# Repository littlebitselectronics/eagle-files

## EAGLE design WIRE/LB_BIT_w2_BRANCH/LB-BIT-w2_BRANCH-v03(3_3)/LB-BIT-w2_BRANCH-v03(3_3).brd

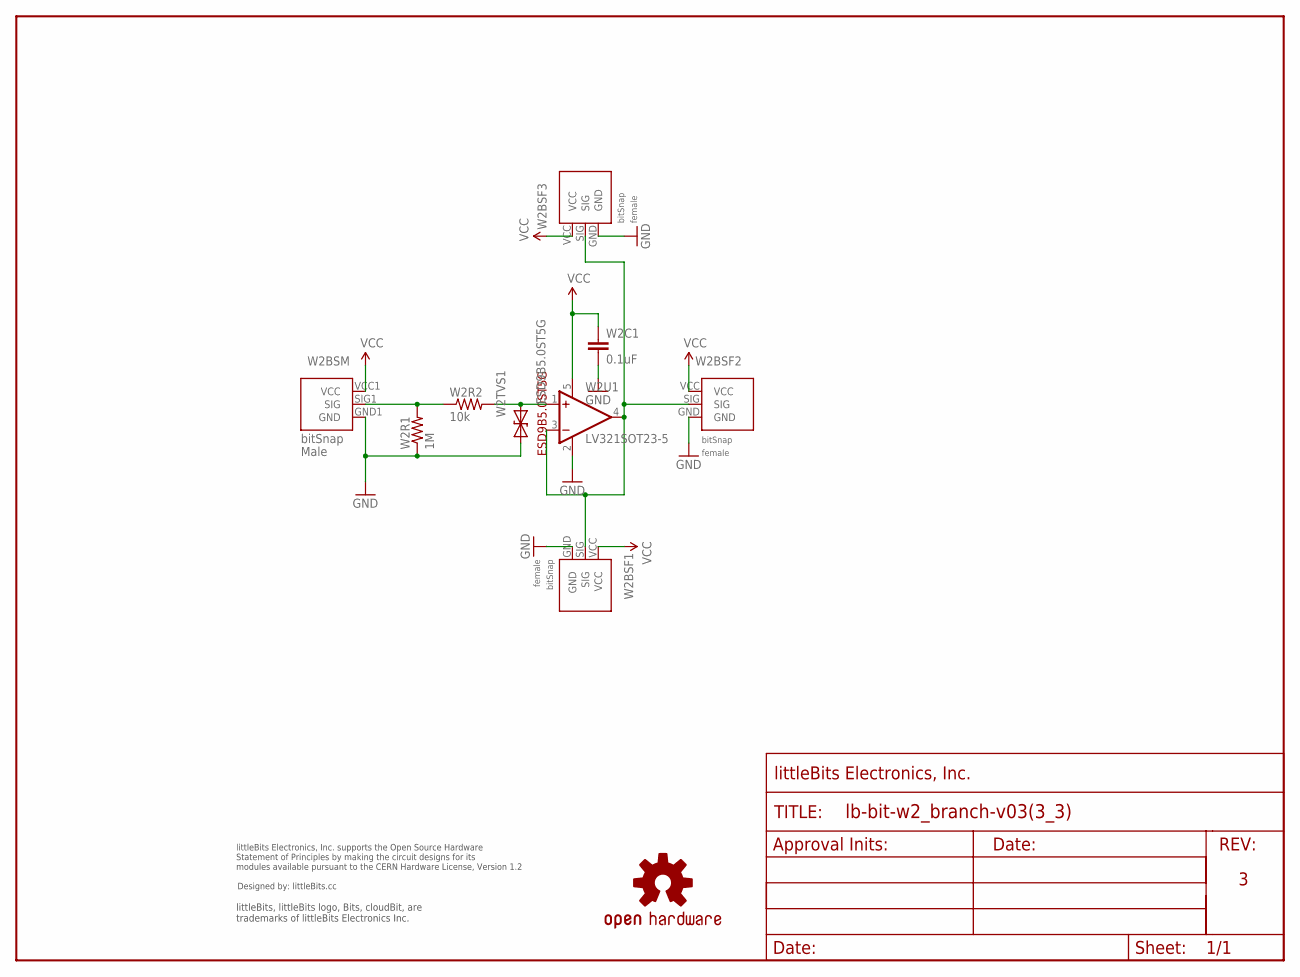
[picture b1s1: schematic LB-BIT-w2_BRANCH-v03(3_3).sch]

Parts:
U$1: OSHWCREDIT
U$2: FRAME-LETTER-OHWOHW; FABDWG01-OHW
U$6: OSHW-LOGOL; OSHW-LOGO-L
W2BSF1, W2BSF2, W2BSF3: BITSNAP_V03_FEMALE
W2BSM: BITSNAP_V03_MALE
W2C1: 0.1uF; CAP-0603
W2R1: 1M; RES-0603
W2R2: 10k; RES-0603
W2TVS1: ESD9B5.0ST5G; SOD-923
W2U1: LV321SOT23-5; SOT23-5

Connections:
GND: W2BSF1.GND, W2BSF2.GND, W2BSF3.GND, W2BSM.GND1 (GND), W2C1.2, W2R1.1, W2TVS1.1 (A), W2U1.2 (V-)
unnamed: W2BSM.SIG1 (SIG), W2R1.2, W2R2.1
unnamed: W2BSF1.SIG, W2BSF2.SIG, W2BSF3.SIG, W2U1.3 (-IN), W2U1.4 (OUT)
unnamed: W2R2.2, W2TVS1.2 (C), W2U1.1 (+IN)
VCC: W2BSF1.VCC, W2BSF2.VCC, W2BSF3.VCC, W2BSM.VCC1 (VCC), W2C1.1, W2U1.5 (V+)

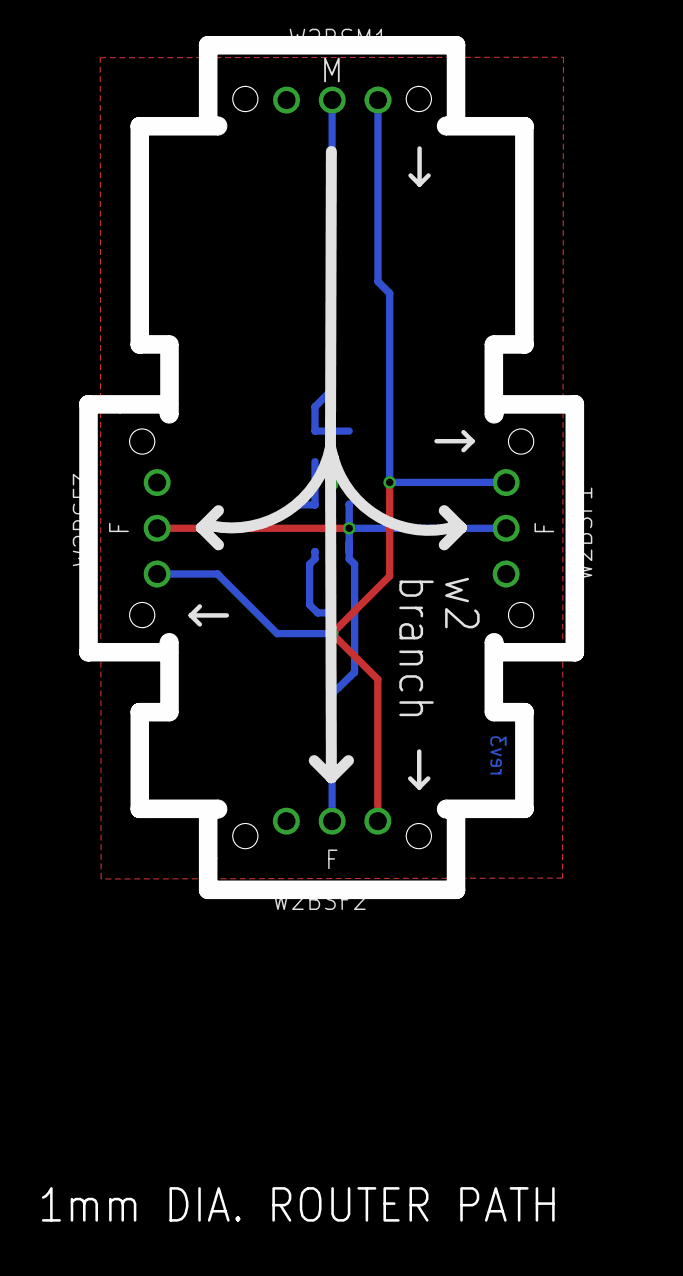
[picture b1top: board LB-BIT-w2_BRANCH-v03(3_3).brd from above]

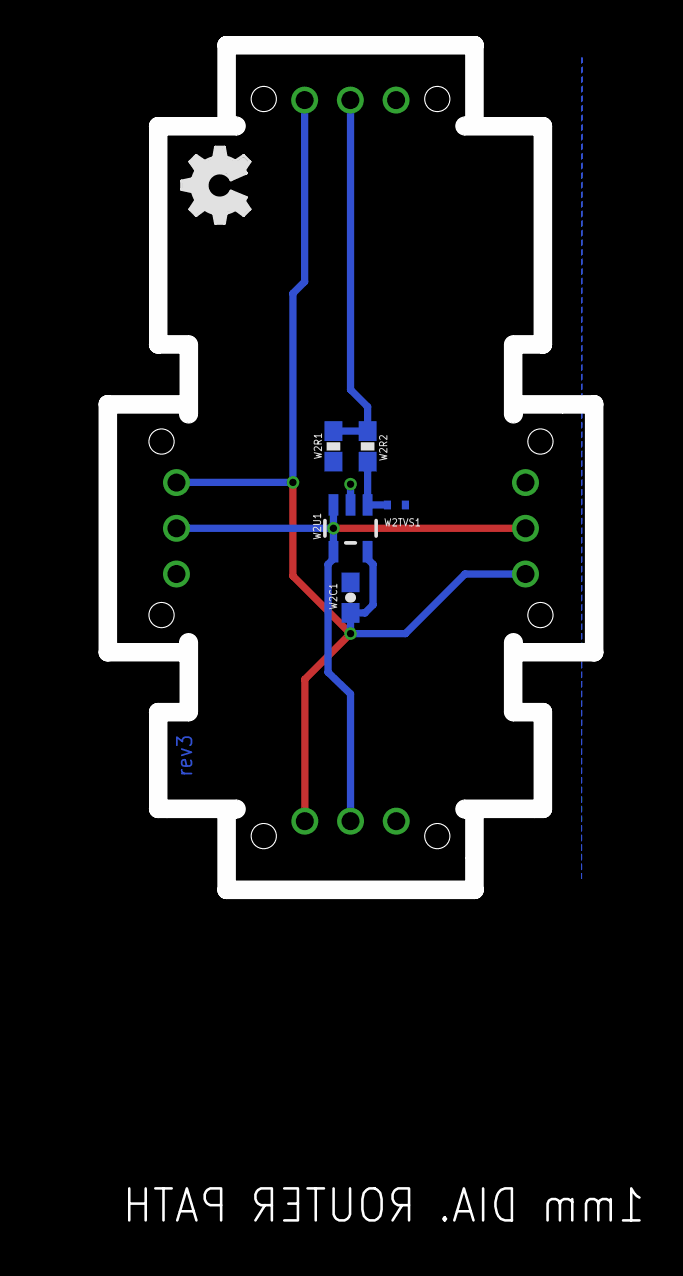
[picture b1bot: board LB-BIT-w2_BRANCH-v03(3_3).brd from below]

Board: 2 copper layers, 27.1 x 47.0 mm, 14 parts (5 on the bottom side), 5 nets.

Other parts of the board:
U$5: OSHW_FILLX150_NOTEXT
U$8: AND/OR_OVERLAY

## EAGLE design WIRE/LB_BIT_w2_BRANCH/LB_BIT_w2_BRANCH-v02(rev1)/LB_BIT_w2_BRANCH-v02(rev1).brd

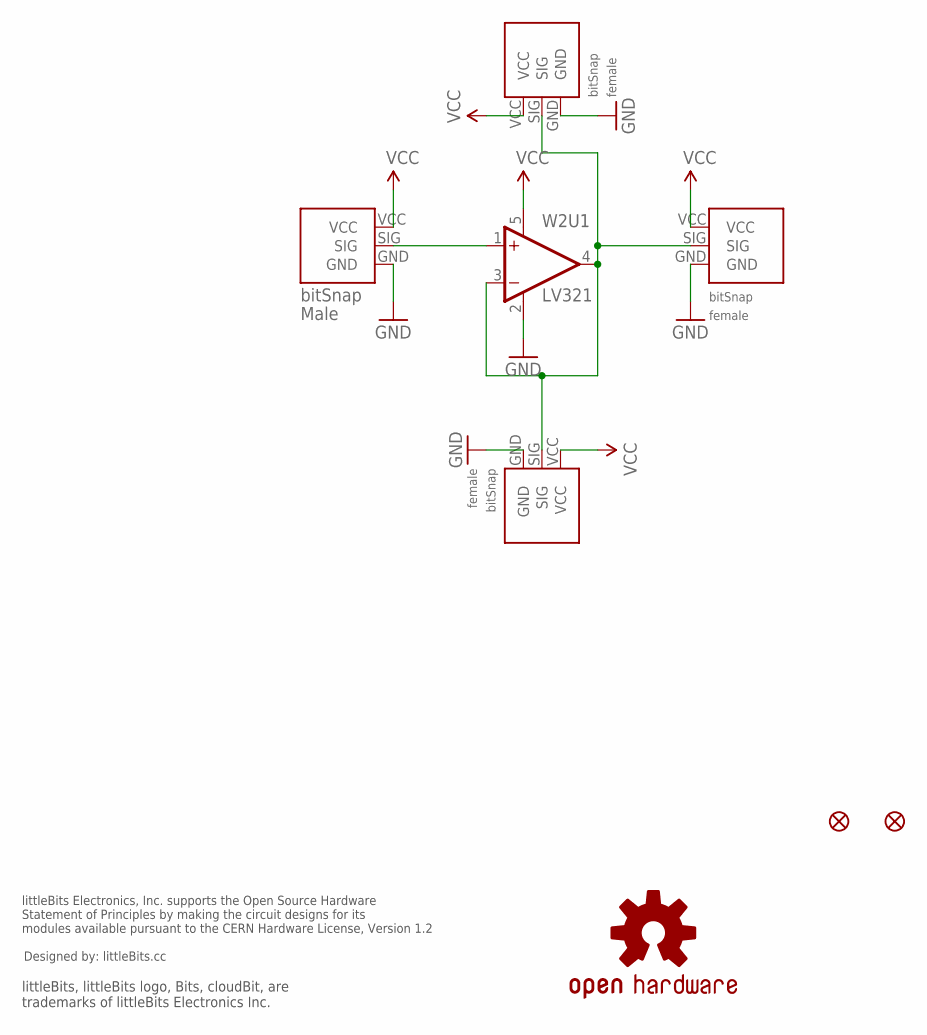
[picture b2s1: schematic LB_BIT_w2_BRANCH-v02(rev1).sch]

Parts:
JP1, JP2: FIDUCIAL1X2; FIDUCIAL-1X2
U$1: OSHWCREDIT
U$6: OSHW-LOGOL; OSHW-LOGO-L
W2BSF1, W2BSF2, W2BSF3: BITSNAP_FEMALE
W2BSM1: BITSNAP_MALE
W2U1: LV321; SC70-5

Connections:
GND: W2BSF1.GND, W2BSF2.GND, W2BSF3.GND, W2BSM1.GND, W2U1.2 (V-)
unnamed: W2BSM1.SIG, W2U1.1 (+IN)
unnamed: W2BSF1.SIG, W2BSF2.SIG, W2BSF3.SIG, W2U1.3 (-IN), W2U1.4 (OUT)
VCC: W2BSF1.VCC, W2BSF2.VCC, W2BSF3.VCC, W2BSM1.VCC, W2U1.5 (V+)

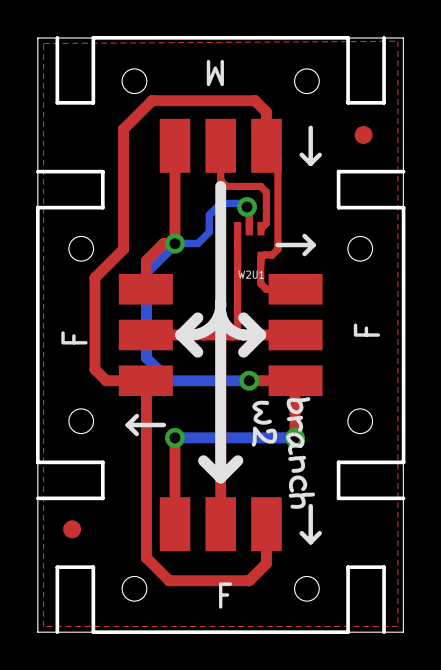
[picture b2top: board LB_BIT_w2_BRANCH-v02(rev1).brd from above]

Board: 2 copper layers, 20.3 x 33.0 mm, 18 parts (0 on the bottom side), 4 nets.

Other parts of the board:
U$5: OSHW_FILLX150_NOTEXT
U$13: B
U$14: R
U$15: A
U$16: N
U$17: C
U$18: H
U$19: W
U$20: 2

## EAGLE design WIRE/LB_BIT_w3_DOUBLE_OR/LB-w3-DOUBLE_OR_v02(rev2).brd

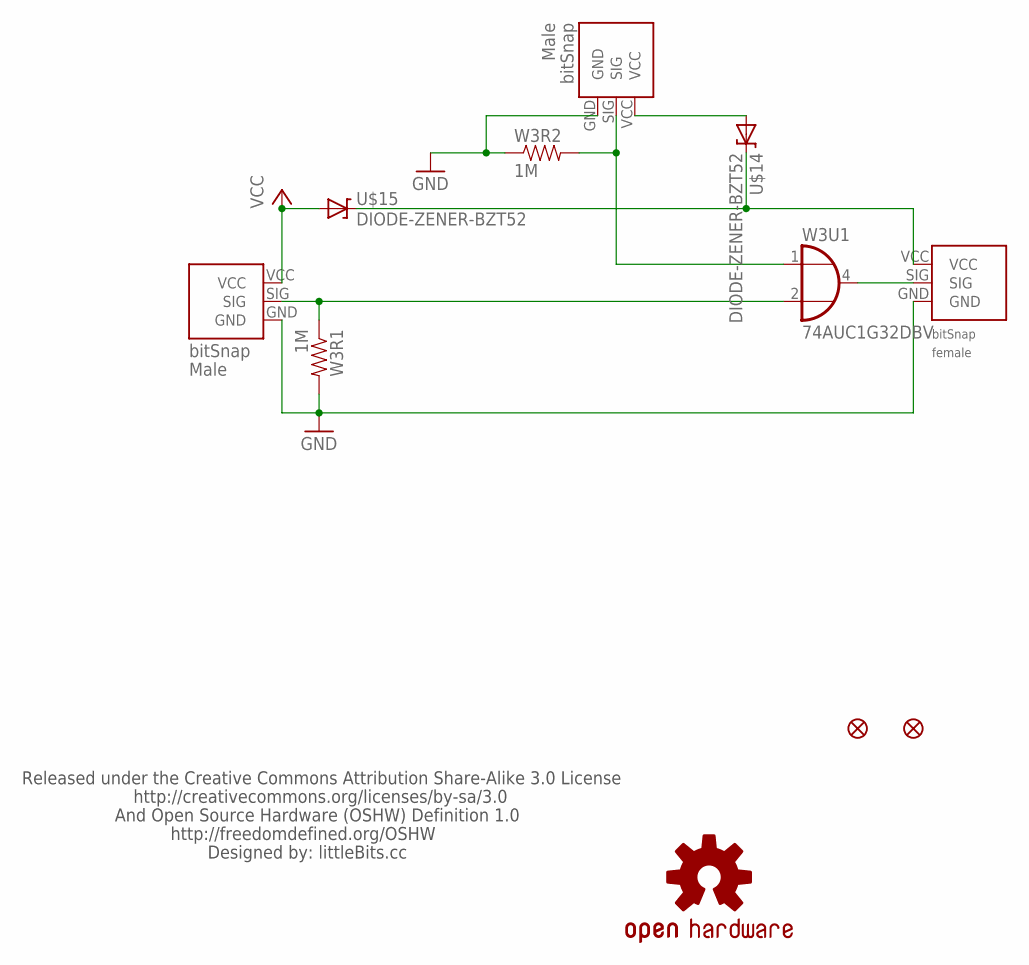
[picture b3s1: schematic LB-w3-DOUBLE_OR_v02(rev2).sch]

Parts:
U$1: LB_CREDITS_V2
U$2: OSHW-LOGOL; OSHW-LOGO-L
U$14, U$15: DIODE-ZENER-BZT52; SOD-323
W3BSF: BITSNAP_FEMALE
W3BSM, W3BSM1: BITSNAP_MALE
W3FD1, W3FD2: FIDUCIAL1X2; FIDUCIAL-1X2
W3R1, W3R2: 1M; 0603-RES
W3U1: 74AUC1G32DBV; SOT23-5

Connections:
GND: W3BSF.GND, W3BSM.GND, W3BSM1.GND, W3R1.2, W3R2.1, W3U1.3 (GND)
unnamed: U$14.2 (A), W3BSM.VCC
unnamed: U$14.1 (C), U$15.1 (C), W3BSF.VCC
unnamed: W3BSM.SIG, W3R2.2, W3U1.1 (I0)
unnamed: W3BSF.SIG, W3U1.4 (O)
unnamed: W3BSM1.SIG, W3R1.1, W3U1.2 (I1)
VCC: U$15.2 (A), W3BSM1.VCC, W3U1.5 (VCC)

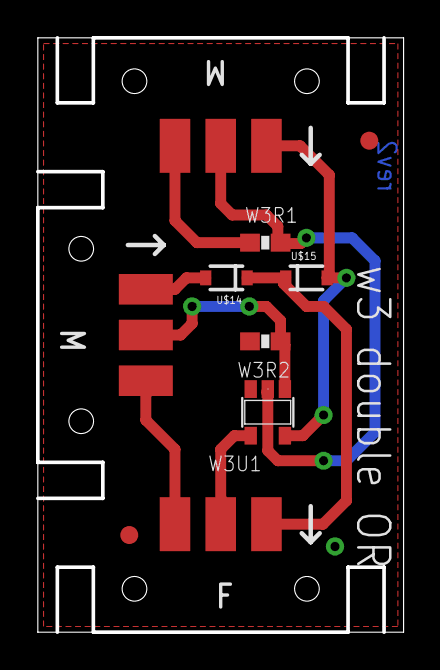
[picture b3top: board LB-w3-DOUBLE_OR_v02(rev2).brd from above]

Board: 2 copper layers, 20.3 x 33.0 mm, 14 parts (0 on the bottom side), 7 nets.

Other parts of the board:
U$6: OSHW_FILLX150_NOTEXT
W3BSM2: LB_V02

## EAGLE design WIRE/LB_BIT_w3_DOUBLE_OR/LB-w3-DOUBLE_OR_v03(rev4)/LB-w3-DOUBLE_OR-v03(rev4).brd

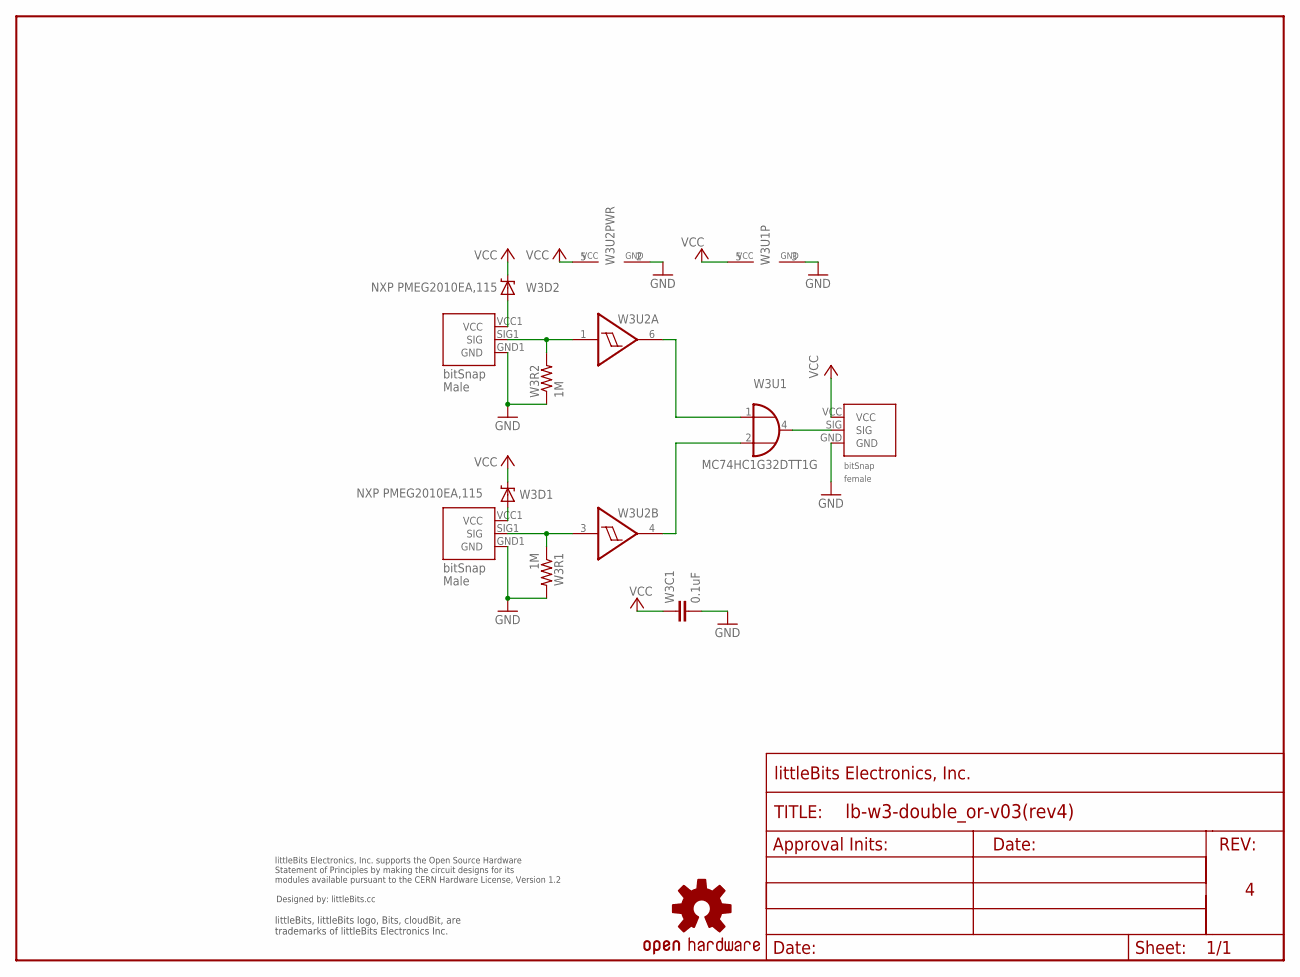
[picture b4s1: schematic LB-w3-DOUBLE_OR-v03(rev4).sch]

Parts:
U$1: OSHWCREDIT
U$2: OSHW-LOGOL; OSHW-LOGO-L
U$16: FRAME-LETTER-OHWOHW; FABDWG01-OHW
W3BSF1: BITSNAP_V03_FEMALE
W3BSM1, W3BSM2: BITSNAP_V03_MALE
W3C1: 0.1uF; CAP-0603
W3D1, W3D2: NXP PMEG2010EA,115; SOD-323
W3R1, W3R2: 1M; 0603-RES
W3U1: 74AUC1G32DBV; SOT23-5
W3U2: SCHMITT_TRIGGER_NON_INVERTING NC7WZ17; SC70-6

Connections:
GND: W3BSF1.GND, W3BSM1.GND1 (GND), W3BSM2.GND1 (GND), W3C1.2, W3R1.2, W3R2.1, W3U1.3 (GND), W3U2.2 (GND)
unnamed: W3BSM2.SIG1 (SIG), W3R1.1, W3U2.3 (I)
unnamed: W3U1.1 (I0), W3U2.6 (O)
unnamed: W3BSM1.VCC1 (VCC), W3D2.2 (A)
unnamed: W3U1.2 (I1), W3U2.4 (O)
unnamed: W3BSM2.VCC1 (VCC), W3D1.2 (A)
unnamed: W3BSM1.SIG1 (SIG), W3R2.2, W3U2.1 (I)
unnamed: W3BSF1.SIG, W3U1.4 (O)
VCC: W3BSF1.VCC, W3C1.1, W3D1.1 (C), W3D2.1 (C), W3U1.5 (VCC), W3U2.5 (VCC)

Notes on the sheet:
MC74HC1G32DTT1G

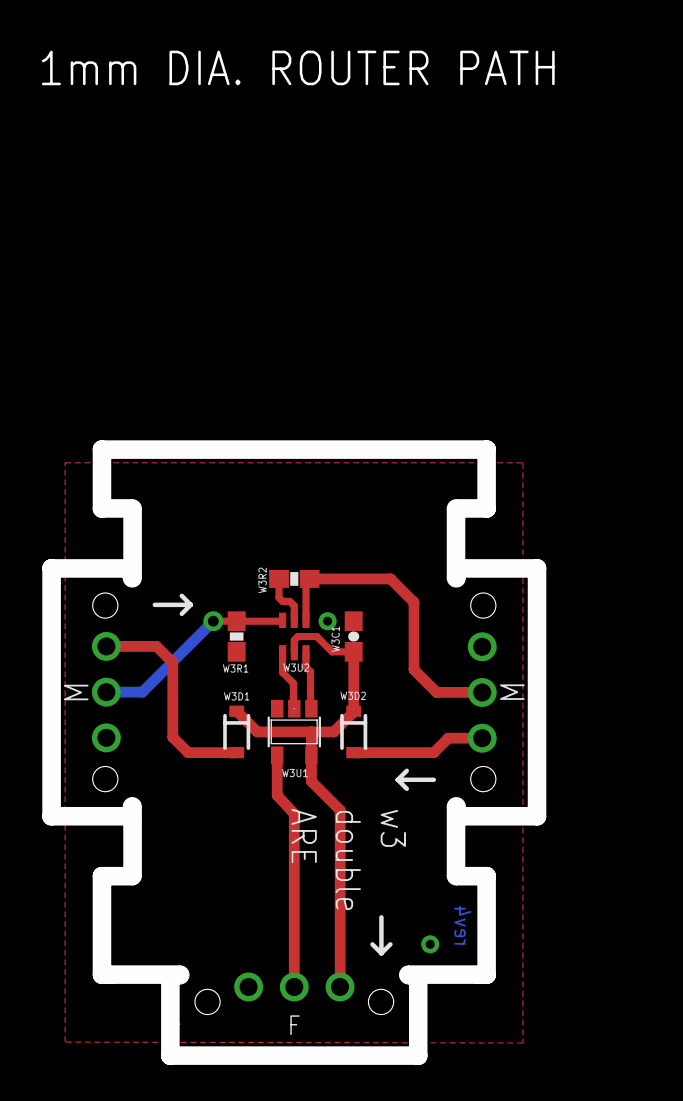
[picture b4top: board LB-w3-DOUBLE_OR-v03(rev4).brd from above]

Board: 2 copper layers, 27.0 x 33.7 mm, 14 parts (0 on the bottom side), 9 nets.

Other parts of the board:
U$6: OSHW_FILLX150_NOTEXT

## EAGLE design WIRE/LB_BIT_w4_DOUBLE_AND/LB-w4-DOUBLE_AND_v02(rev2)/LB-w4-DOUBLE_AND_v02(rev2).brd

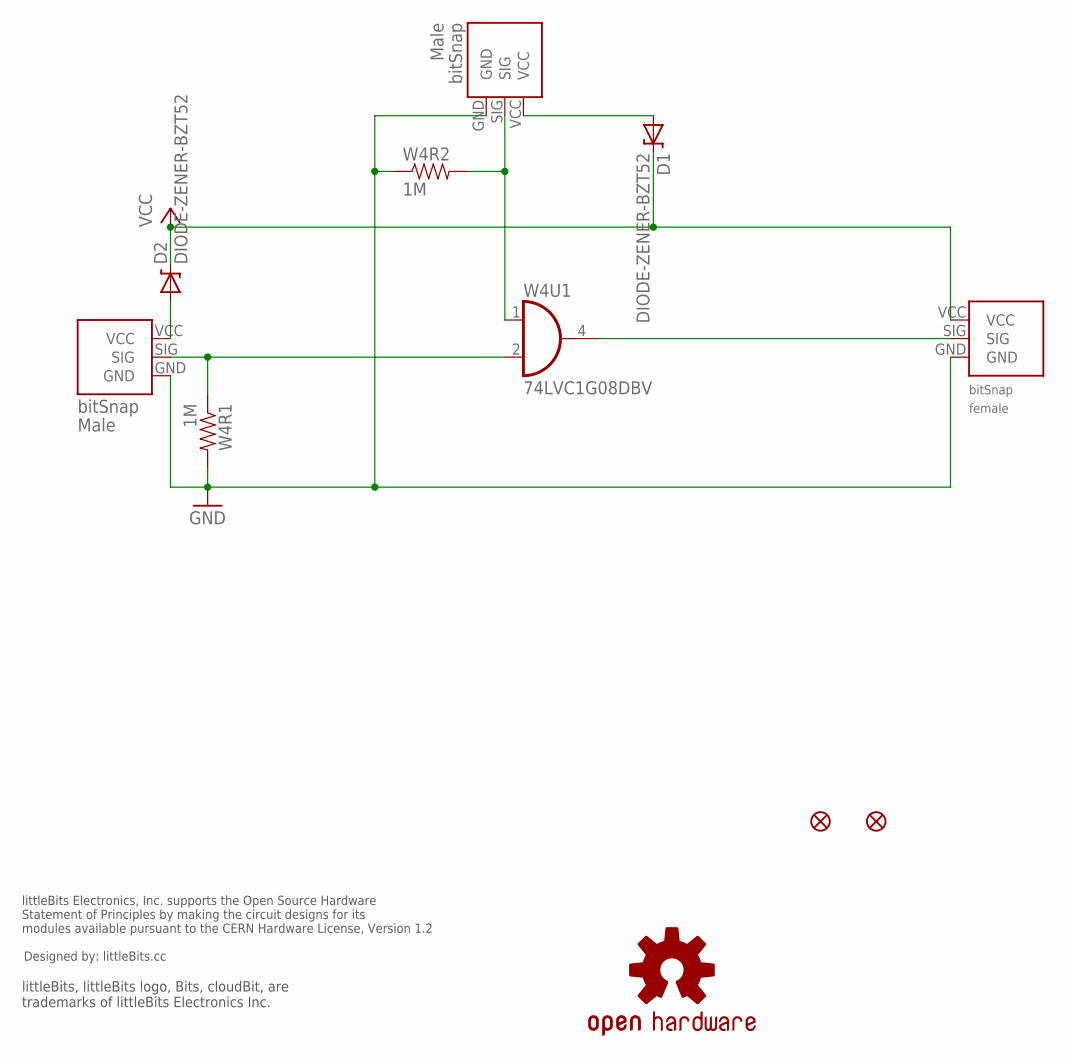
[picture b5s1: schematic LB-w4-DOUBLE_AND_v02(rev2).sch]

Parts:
D1, D2: DIODE-ZENER-BZT52; SOD-323
U$1: OSHW-LOGOL; OSHW-LOGO-L
U$2: OSHWCREDIT
W4BSF: BITSNAP_FEMALE
W4BSM1, W4BSM2: BITSNAP_MALE
W4FD1, W4FD2: FIDUCIAL1X2; FIDUCIAL-1X2
W4R1, W4R2: 1M; 0603-RES
W4U1: 74LVC1G08DBV; SOT23-5

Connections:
GND: W4BSF.GND, W4BSM1.GND, W4BSM2.GND, W4R1.2, W4R2.1, W4U1.3 (GND)
unnamed: W4BSF.SIG, W4U1.4 (O)
unnamed: D1.2 (A), W4BSM2.VCC
unnamed: D2.2 (A), W4BSM1.VCC
unnamed: W4BSM2.SIG, W4R2.2, W4U1.1 (I0)
unnamed: W4BSM1.SIG, W4R1.1, W4U1.2 (I1)
VCC: D1.1 (C), D2.1 (C), W4BSF.VCC, W4U1.5 (VCC)

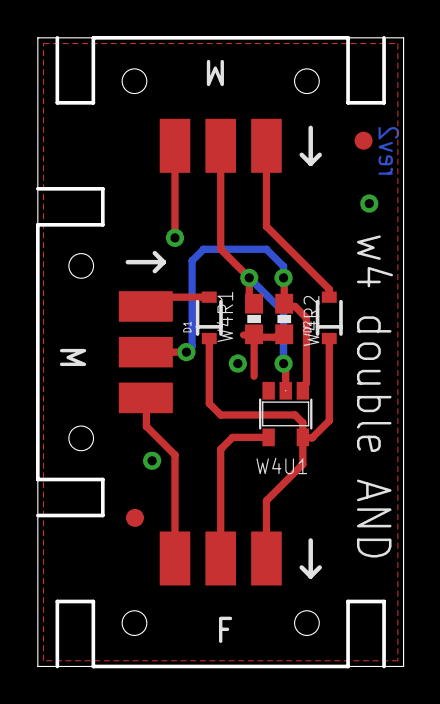
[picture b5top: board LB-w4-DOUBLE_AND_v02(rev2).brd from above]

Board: 2 copper layers, 20.3 x 34.9 mm, 13 parts (0 on the bottom side), 7 nets.

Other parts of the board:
U$15: OSHW_FILLX150_NOTEXT

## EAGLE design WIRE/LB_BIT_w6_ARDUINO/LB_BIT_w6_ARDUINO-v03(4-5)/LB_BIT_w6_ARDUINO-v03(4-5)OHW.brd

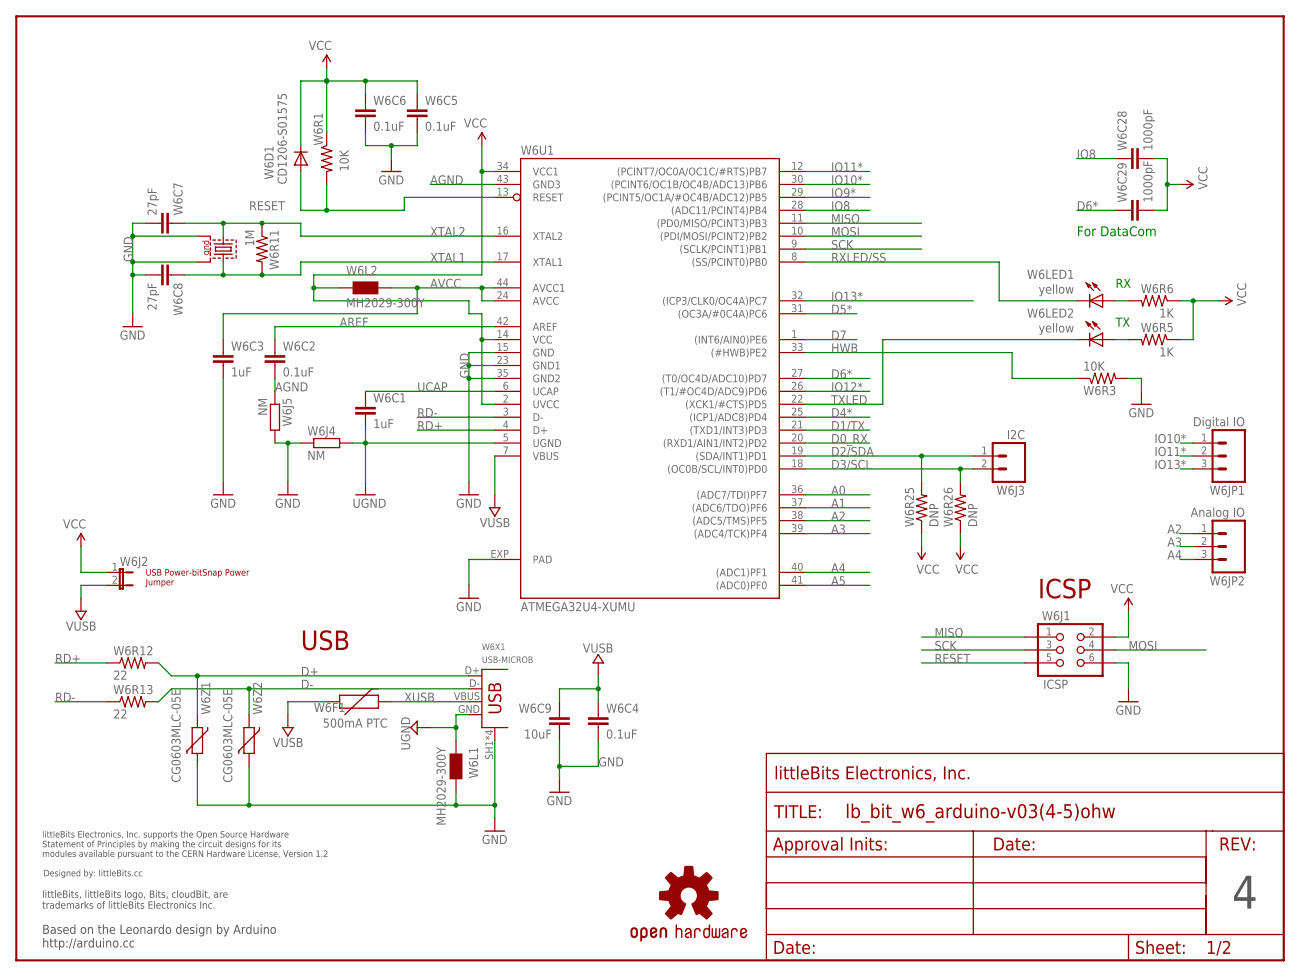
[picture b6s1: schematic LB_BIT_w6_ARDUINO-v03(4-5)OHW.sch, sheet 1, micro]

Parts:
FRAME2: FRAME-LETTER-OHWOHW; FABDWG01-OHW
U$52: OSHW-LOGOL; OSHW-LOGO-L
U$67: OSHWCREDIT
W6C1, W6C3: 1uF; CAP-0603
W6C2, W6C4, W6C5, W6C6: 0.1uF; CAP-0603
W6C7, W6C8: 27pF; CAP-0603
W6C9: 10uF; CAP-0805
W6C28, W6C29: 1000pF; CAP-0603
W6D1: CD1206-S01575; MINIMELF
W6F1: 500mA PTC; PTC-1206
W6J1: ICSP; 2X03
W6J2: JUMPER-2SMD-NO; SJ_2S-NO
W6J3: I2C; SIP2-SM-0.1IN
W6J4, W6J5: NM; R0402
W6JP1: Digital IO; 1X03
W6JP2: Analog IO; 1X03
W6L1, W6L2: MH2029-300Y; 0805
W6LED1, W6LED2: yellow; LED-1206
W6Q1: 16MHz; CRYSTAL-SMD-7B-SERIES-5X3.2MM
W6R1, W6R3: 10K; RES-0603
W6R5, W6R6: 1K; RES-0603
W6R11: 1M; RES-0603
W6R12, W6R13: 22; RES-0603
W6R25, W6R26: DNP; RES-0603
W6U1: ATMEGA32U4-XUMU; QFN44ML7X7
W6X1: USB-MICROB; USB-MICROB-AUK-DRILLS
W6Z1, W6Z2: CG0603MLC-05E; CT/CN0603

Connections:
A0: W6U1.36 ((ADC7/TDI)PF7); also elsewhere on the board
A1: W6U1.37 ((ADC6/TDO)PF6); also elsewhere on the board
A2: W6JP2.1, W6U1.38 ((ADC5/TMS)PF5)
A3: W6JP2.2, W6U1.39 ((ADC4/TCK)PF4)
A4: W6JP2.3, W6U1.40 ((ADC1)PF1)
A5: W6U1.41 ((ADC0)PF0)
AGND: W6C2.2, W6J5.1, W6U1.43 (GND3)
AREF: W6C2.1, W6U1.42 (AREF)
AVCC: W6C3.1, W6L2.2, W6U1.24 (AVCC), W6U1.44 (AVCC1)
D0_RX: W6U1.20 ((RXD1/AIN1/INT2)PD2); also elsewhere on the board
D1/TX: W6U1.21 ((TXD1/INT3)PD3); also elsewhere on the board
D2/SDA: W6J3.1, W6R25.2, W6U1.19 ((SDA/INT1)PD1)
D3/SCL: W6J3.2, W6R26.2, W6U1.18 ((OC0B/SCL/INT0)PD0)
D4*: W6U1.25 ((ICP1/ADC8)PD4)
D5*: W6U1.31 ((OC3A/#0C4A)PC6); also elsewhere on the board
D6*: W6C29.1, W6U1.27 ((T0/OC4D/ADC10)PD7)
D7: W6U1.1 ((INT6/AIN0)PE6)
D+: W6R12.2, W6X1.D+, W6Z1.1
D-: W6R13.2, W6X1.D-, W6Z2.1
GND: W6C3.2, W6C4.2, W6C5.2, W6C6.2, W6C7.2, W6C8.2, W6C9.2, W6J1.6, W6J4.1, W6J5.2, W6L1.2, W6Q1.P$2 (2), W6Q1.P$4 (4), W6R3.2, W6U1.15 (GND), W6U1.23 (GND1), W6U1.35 (GND2), W6U1.EXP (PAD), W6X1.SH1 (SH), W6X1.SH2 (SH), W6X1.SH3 (SH), W6X1.SH4 (SH), W6Z1.2, W6Z2.2; also elsewhere on the board
HWB: W6R3.1, W6U1.33 ((#HWB)PE2)
IO8: W6C28.1, W6U1.28 ((ADC11/PCINT4)PB4)
IO9*: W6U1.29 ((PCINT5/OC1A/#OC4B/ADC12)PB5); also elsewhere on the board
IO10*: W6JP1.1, W6U1.30 ((PCINT6/OC1B/OC4B/ADC13)PB6)
IO11*: W6JP1.2, W6U1.12 ((PCINT7/OC0A/OC1C/#RTS)PB7)
IO12*: W6U1.26 ((T1/#OC4D/ADC9)PD6)
IO13*: W6JP1.3, W6U1.32 ((ICP3/CLK0/OC4A)PC7)
MISO: W6J1.1, W6U1.11 ((PD0/MISO/PCINT3)PB3)
MOSI: W6J1.4, W6U1.10 ((PDI/MOSI/PCINT2)PB2)
unnamed: W6LED1.A, W6R6.2
unnamed: W6LED2.A, W6R5.2
RD+: W6R12.1, W6U1.4 (D+)
RD-: W6R13.1, W6U1.3 (D-)
RESET: W6D1.A, W6J1.5, W6R1.2, W6U1.13 (RESET)
RXLED/SS: W6LED1.C, W6U1.8 ((SS/PCINT0)PB0)
SCK: W6J1.3, W6U1.9 ((SCLK/PCINT1)PB1)
TXLED: W6LED2.C, W6U1.22 ((XCK1/#CTS)PD5)
UCAP: W6C1.1, W6U1.6 (UCAP)
UGND: W6C1.2, W6J4.2, W6L1.1, W6U1.5 (UGND), W6X1.GND
VCC: W6C5.1, W6C6.1, W6C28.2, W6C29.2, W6D1.C, W6J1.2, W6J2.1, W6L2.1, W6R1.1, W6R5.1, W6R6.1, W6R25.1, W6R26.1, W6U1.2 (UVCC), W6U1.14 (VCC), W6U1.34 (VCC1); also elsewhere on the board
VUSB: W6C4.1, W6C9.1, W6F1.1, W6J2.2, W6U1.7 (VBUS)
XTAL1: W6C8.1, W6Q1.P$3 (3), W6R11.2, W6U1.17 (XTAL1)
XTAL2: W6C7.1, W6Q1.P$1 (1), W6R11.1, W6U1.16 (XTAL2)
XUSB: W6F1.2, W6X1.VBUS

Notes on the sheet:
ICSP
USB
USB Power-bitSnap Power Jumper
For DataCom
Based on the Leonardo design by Arduino http://arduino.cc

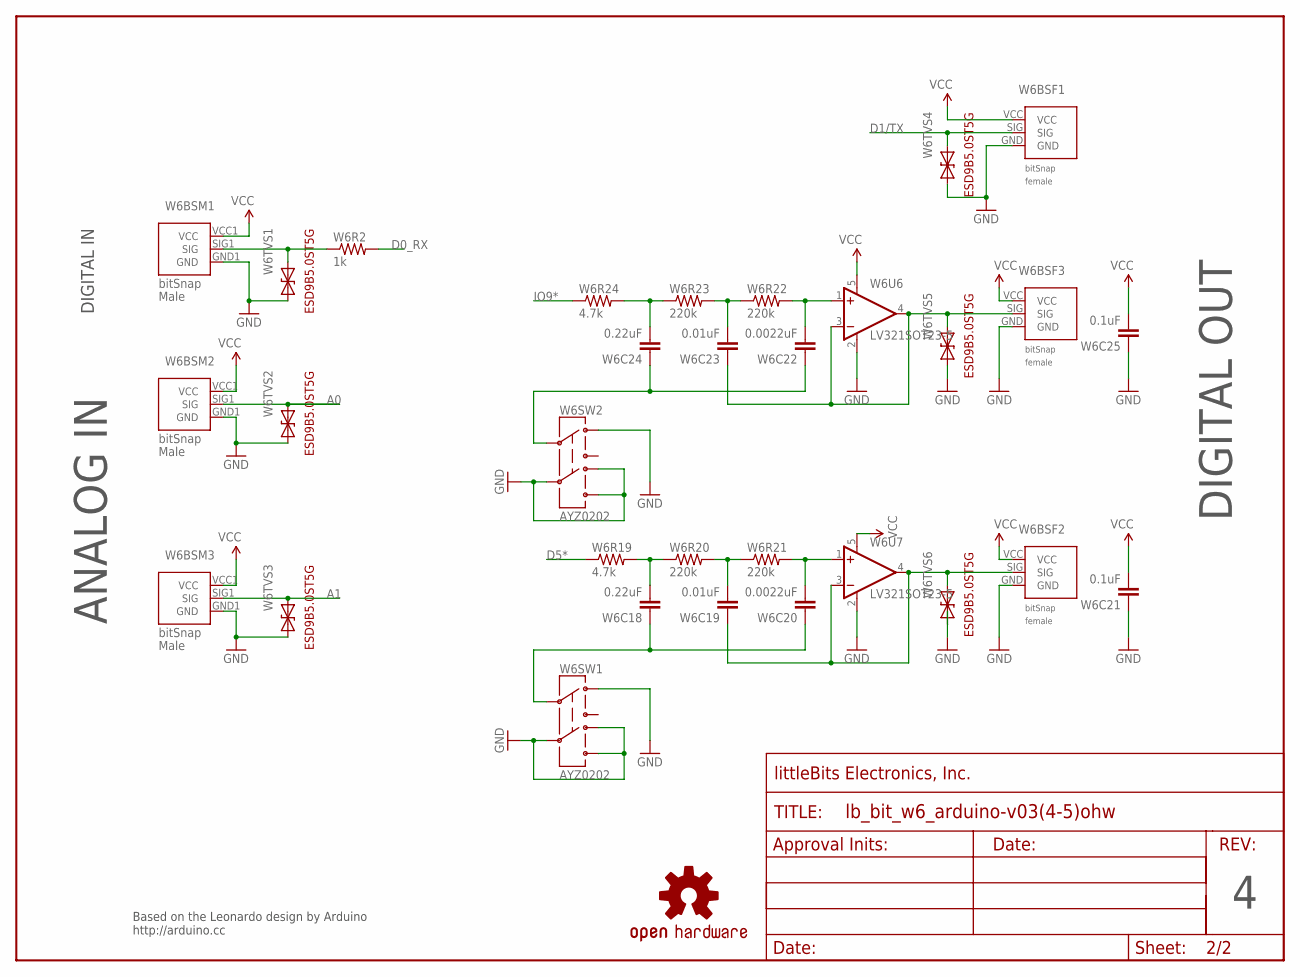
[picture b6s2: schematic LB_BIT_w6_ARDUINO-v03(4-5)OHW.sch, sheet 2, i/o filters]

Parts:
U$54: FRAME-LETTER-OHWOHW; FABDWG01-OHW
U$70: OSHW-LOGOL; OSHW-LOGO-L
W6BSF1, W6BSF2, W6BSF3: BITSNAP_V03_FEMALE
W6BSM1, W6BSM2, W6BSM3: BITSNAP_V03_MALE
W6C18, W6C24: 0.22uF; CAP-0603
W6C19, W6C23: 0.01uF; CAP-0603
W6C20, W6C22: 0.0022uF; CAP-0603
W6C21, W6C25: 0.1uF; CAP-0603
W6R2: 1k; RES-0603
W6R19, W6R24: 4.7k; RES-0603
W6R20, W6R21, W6R22, W6R23: 220k; RES-0603
W6SW1, W6SW2: AYZ0202
W6TVS1, W6TVS2, W6TVS3, W6TVS4, W6TVS5, W6TVS6: DIODE-TVSSOD-923; SOD-923
W6U6, W6U7: LV321SOT23-5; SOT23-5

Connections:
A0: W6BSM2.SIG1 (SIG), W6TVS2.2 (C); also elsewhere on the board
A1: W6BSM3.SIG1 (SIG), W6TVS3.2 (C); also elsewhere on the board
D0_RX: W6R2.2; also elsewhere on the board
D1/TX: W6BSF1.SIG, W6TVS4.2 (C); also elsewhere on the board
D5*: W6R19.1; also elsewhere on the board
GND: W6BSF1.GND, W6BSF2.GND, W6BSF3.GND, W6BSM1.GND1 (GND), W6BSM2.GND1 (GND), W6BSM3.GND1 (GND), W6C21.1, W6C25.1, W6SW1.1, W6SW1.4, W6SW1.5, W6SW1.6, W6SW2.1, W6SW2.4, W6SW2.5, W6SW2.6, W6TVS1.1 (A), W6TVS2.1 (A), W6TVS3.1 (A), W6TVS4.1 (A), W6TVS5.1 (A), W6TVS6.1 (A), W6U6.2 (V-), W6U7.2 (V-); also elsewhere on the board
IO9*: W6R24.1; also elsewhere on the board
unnamed: W6C18.1, W6C20.1, W6SW1.2
unnamed: W6BSM1.SIG1 (SIG), W6R2.1, W6TVS1.2 (C)
unnamed: W6C18.2, W6R19.2, W6R20.1
unnamed: W6C19.2, W6R20.2, W6R21.1
unnamed: W6C20.2, W6R21.2, W6U7.1 (+IN)
unnamed: W6BSF2.SIG, W6C19.1, W6TVS6.2 (C), W6U7.3 (-IN), W6U7.4 (OUT)
unnamed: W6BSF3.SIG, W6C23.1, W6TVS5.2 (C), W6U6.3 (-IN), W6U6.4 (OUT)
unnamed: W6C22.2, W6R22.2, W6U6.1 (+IN)
unnamed: W6C24.2, W6R23.1, W6R24.2
unnamed: W6C23.2, W6R22.1, W6R23.2
unnamed: W6C22.1, W6C24.1, W6SW2.2
VCC: W6BSF1.VCC, W6BSF2.VCC, W6BSF3.VCC, W6BSM1.VCC1 (VCC), W6BSM2.VCC1 (VCC), W6BSM3.VCC1 (VCC), W6C21.2, W6C25.2, W6U6.5 (V+), W6U7.5 (V+); also elsewhere on the board

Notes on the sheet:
ANALOG IN
DIGITAL OUT
DIGITAL IN
Based on the Leonardo design by Arduino http://arduino.cc

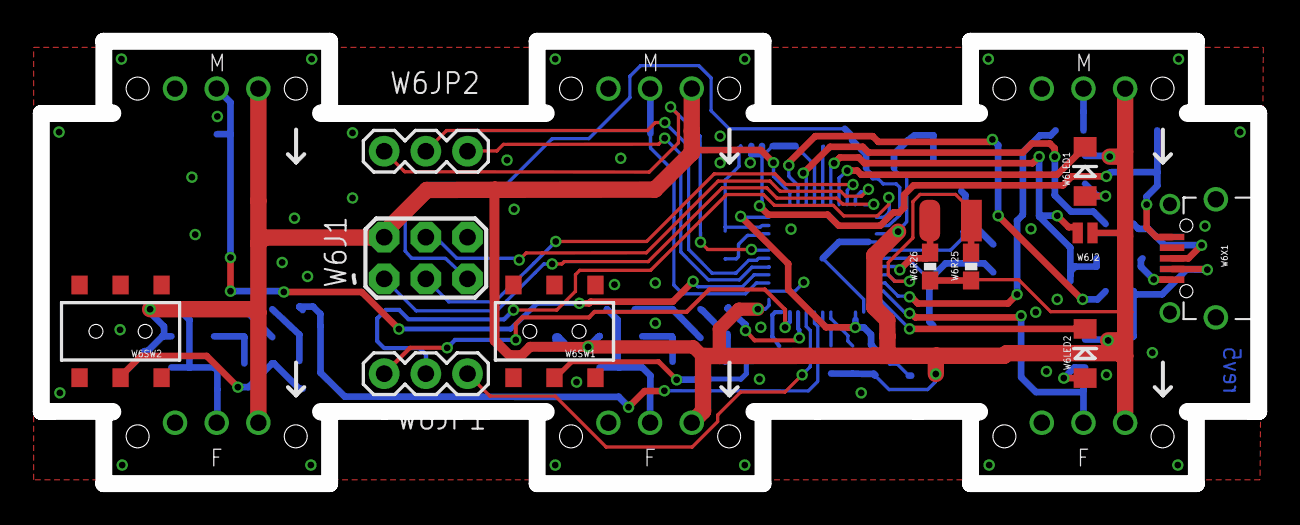
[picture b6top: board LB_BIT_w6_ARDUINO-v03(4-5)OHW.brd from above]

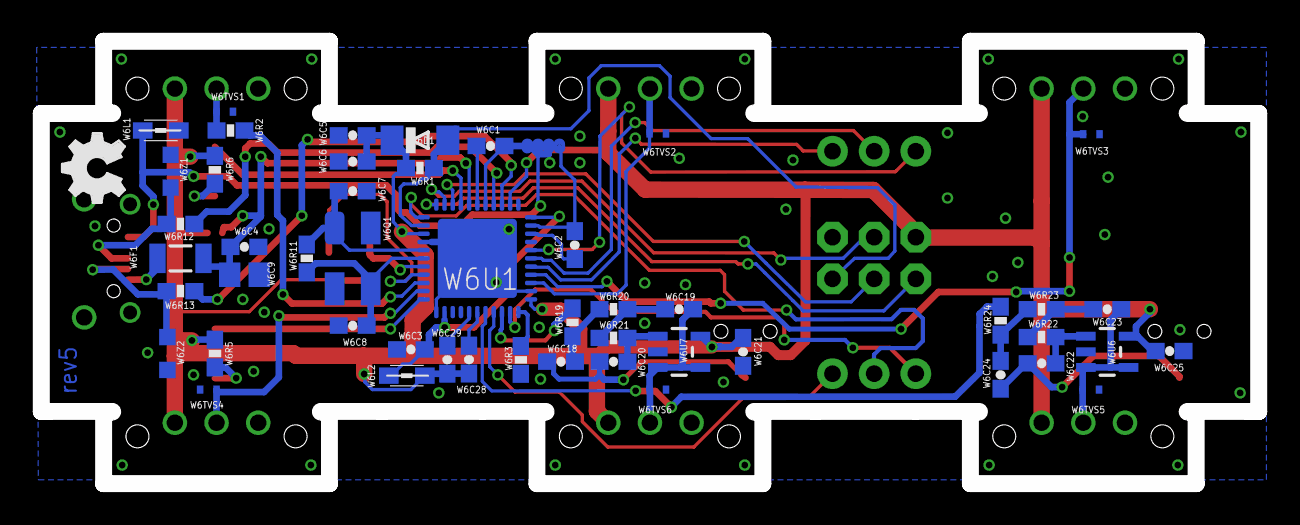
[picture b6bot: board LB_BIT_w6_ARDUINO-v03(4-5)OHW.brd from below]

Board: 2 copper layers, 74.2 x 27.0 mm, 77 parts (51 on the bottom side), 51 nets.

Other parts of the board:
DRILEGEND: DRILEGEND
U$5: OSHW_FILLX150_NOTEXT
U$29: -

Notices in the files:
parts and their libraries:
LITTLEBITS: modules available pursuant to the CERN Hardware License,
Version 1.2
SparkFun_NEW: Licensing: CC v3.0 Share-Alike You are welcome to use this library for commercial purposes.
LITTLEBITS: modules available pursuant to the CERN Hardware License, Version 1.2
